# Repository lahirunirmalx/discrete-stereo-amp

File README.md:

# Stereo class-AB amplifier, discrete 12 V supply, volume and headphone boards

A hobby / learning project: a two-channel 1 W class-AB amplifier built from BC547/BC557/BD139/BD140,
its own transformer-fed discrete supply, a volume board and a headphone board, all on one fab panel. It grew
out of a review of a one-transistor "speaker in the collector" amp, which could not be fixed by changing
values. Every number here comes from ngspice; **no board has been built or measured yet** (revision 1.3 is a
prototype design). Release 2 rebuilt the amp front end for ten times less distortion, closed the supply's
regulation loop, added a VU meter tap and the headphone board. Revision 1.3 is the result of a second design
review: an output inductor for stability into capacitive loads, a fail-safe bias trimmer, input protection on
the amp, a correctly sized supply fuse and a headphone switch rated for speaker current.

| Amp | PSU | Volume | Headphone |
|---|---|---|---|
|  |  |  |  |

More views in [docs/images/](docs/images/): top-down 3D renders and the single-sided layouts. Logo and banner: `logo.svg` / `logo.png` / `logo-1024.png` and `banner.svg` / `banner.png` (1280 x 640, the GitHub social-preview size).

## Schematics

| Amp (both channels) | PSU | Volume | Headphone |
|---|---|---|---|
|  |  |  |  |

PDFs of all four are in the release zip (`schematics/`).

## Boards (2-layer layouts, top view, both copper layers)

| Amp, wide 134 x 86 mm | Amp, compact 100 x 98 mm | PSU 90 x 58 mm | Volume 42 x 26 mm | Headphone 42 x 30 mm |
|---|---|---|---|---|
|  |  |  |  |  |

## What it does

| | |
|---|---|
| Output | 1.2 W into 8 ohm and 1.5 W into 4 ohm at the onset of clipping (per channel, 12 V); 0.29 W into 8 ohm at 0.02 to 0.05% THD, 52 mW into 4 ohm at 0.013% |
| Gain / input | 23 (27 dB), 46k input impedance, for a 10k log pot |
| Idle current | output stage 21 mA per channel after setting the trimmer (7 to 10 mV across a 0.47 ohm emitter resistor; trimmer range 2 to 70 mA); about 33 mA per channel from the supply |
| Bandwidth | 20 Hz (8 ohm) / 34 Hz (4 ohm) to 108 kHz, -0.13 dB at 20 kHz |
| Stability | loop phase margin 65 degrees or more for any load from open to 2.2 uF (2.2 uH + 10 ohm output inductor) |
| Protection | amp: resettable fuse + reverse-polarity diode on the 12 V input, bias trimmer limited to 70 mA and fail-safe; PSU: 2 A clamp + 1.6 A slow fuse |
| Supply | 12 to 15 VAC transformer (1.5 A for full power) or 12 V DC in; closed-loop 12.0 V out (trimmer 11.4 to 12.7 V), 0.14 V dip on a 1 A step, 2 A clamp |
| Headphones | DPDT toggle switch speakers / phones, 120 ohm series (8 mW into 32 ohm), DIRECT jumpers, 3.5 mm jack or panel jack header |
| VU meter | 1x3 header on the amp, 1k in series with each speaker node (2.8 Vrms at 1 W) |
| Boards | amp 134 x 86 mm (or the compact 100 x 98 mm variant for the 100 x 100 fab tier), PSU 90 x 58 mm, volume 42 x 26 mm, headphone 42 x 30 mm; 2-layer panel 156 x 156 mm; single-sided variants |
| Parts | 151 through-hole parts with 1206 / SOD / SMA / SOT-23 twins on the same pads; 38 solder jumpers (output pinouts, headphone DIRECT) |

## Design rules this project keeps

1. **Modular.** Every board works alone; none depends on another. Build the amp only, add the volume board or the PSU later.
2. **Your parts, your build.** Every passive has through-hole pads plus a 1206 / SOD / SMA twin; every output transistor sits behind a 3x3 solder-jumper pinout block; the BOM lists at least three substitutes per transistor. Fit what you have.
3. **Debuggable by a beginner.** Every board carries labelled test points with the expected voltage printed next to them, and the bring-up guide walks through them in order.

Any change to this project is checked against these three before it is merged.

## Build it board by board

Every board works on its own; nothing is required by another board.

| You build | You need | What you get |
|---|---|---|
| Amp only | any 12 V DC supply of 1 A (wall adapter, bench supply) into "12V IN"; a phone, PC or DAC into the "IN L G R" header; speakers on the terminals | a working stereo amp; the source's own volume control sets the level (a phone at full volume will clip, so turn it down) |
| Amp + volume board | as above, plus the two 3-pin cables | a volume knob (and the front-panel LED position) |
| Amp + PSU | a 12 to 15 VAC transformer into the PSU, or 12 V DC into its "DC IN"; PSU "DC OUT" to the amp | a regulated, clamped, fused supply with the power LED |
| Amp + headphone board | three wires from the amp's speaker terminals to "FROM AMP", speakers on the headphone board's terminals | a speakers / phones switch and a jack |
| VU meters | any meter on the amp's "VU L G R" header | level display; nothing else changes |
| All four | the panel | the complete desk amp |

Two amp layouts carry the same circuit: the wide one (134 x 86 mm, matches the PSU plus headphone-and-volume
column on the panel) and the compact one (100 x 98 mm, fits JLCPCB's 100 x 100 mm tier when ordered alone).
Choose by price; there is no electrical difference.

## Documents

1. [docs/01-theory-of-operation.md](docs/01-theory-of-operation.md): every block explained for a first build, with the voltages to expect.
2. [docs/02-simulation-results.md](docs/02-simulation-results.md): all the ngspice tables, including the rejected candidates, the release 2 front end and supply (2.7 to 2.9) and the revision 1.3 loop-gain work (2.10).
3. [docs/03-design-review.md](docs/03-design-review.md): what was checked, what was found, what is not verified.
4. [docs/04-build-and-bringup.md](docs/04-build-and-bringup.md): assembly order, first power-up, bias setting, test points, troubleshooting.
5. [ORDER_GUIDE.md](ORDER_GUIDE.md): ordering the panel, substitutes, matching, tolerances.
6. [docs/05-preamp-study.md](docs/05-preamp-study.md): does a preamp stage help a line-level desk amp? (No; where it would.)
7. [docs/KNOWN_ISSUES.md](docs/KNOWN_ISSUES.md) and [docs/CHANGELOG.md](docs/CHANGELOG.md).
8. Interactive: [amp channel in CircuitJS](https://www.falstad.com/circuit/circuitjs.html?cct=$%201%200.000005%2010.20027730826997%2050%205%2050%0Av%2064%20480%2064%2064%200%200%2040%2012%200%200%200.5%0Ag%2064%20480%2064%20512%200%0Aw%2064%2064%20208%2064%200%0Aw%20208%2064%20288%2064%200%0Aw%20288%2064%20352%2064%200%0Aw%20352%2064%20528%2064%200%0Aw%20528%2064%20816%2064%200%0Av%20128%20480%20128%20368%200%201%201000%200.1%200%200%200.5%0Ag%20128%20480%20128%20512%200%0Ar%20128%20368%20192%20368%200%202500%0Ac%20192%20368%20256%20368%200%202.2e-06%200%200%0Ar%20208%2064%20208%20176%200%2047000%0Ar%20208%20176%20208%20480%200%2047000%0Ag%20208%20480%20208%20512%200%0Ac%20240%20176%20240%20480%200%204.7e-05%200%200%0Ag%20240%20480%20240%20512%200%0Aw%20208%20176%20240%20176%200%0Aw%20240%20176%20272%20176%200%0Ar%20272%20176%20272%20368%200%2047000%0Aw%20256%20368%20272%20368%200%0Aw%20272%20368%20304%20368%200%0At%20304%20368%20352%20368%200%201%200%200%20290%0At%20496%20368%20448%20368%200%201%200%200%20290%0Aw%20352%20384%20352%20416%200%0Aw%20352%20416%20400%20416%200%0Aw%20400%20416%20448%20416%200%0Aw%20448%20384%20448%20416%200%0Ar%20400%20416%20400%20480%200%2010000%0Ag%20400%20480%20400%20512%200%0Aw%20448%20352%20448%20320%200%0Aw%20448%20320%20528%20320%200%0Aw%20528%20320%20528%2064%200%0Ar%20288%2064%20288%20160%200%204700%0Aw%20288%20160%20288%20192%200%0Aw%20288%20192%20288%20240%200%0Aw%20288%20240%20352%20240%200%0Aw%20352%20240%20352%20352%200%0Aw%20496%20368%20528%20368%200%0Aw%20528%20368%20544%20368%200%0Ar%20544%20368%20608%20368%200%2022000%0A207%20608%20368%20640%20368%204%20out%0Ar%20528%20368%20528%20416%200%201000%0Ac%20528%20416%20528%20480%200%200.00022%200%200%0Ag%20528%20480%20528%20512%200%0At%20320%20192%20368%20192%200%20-1%200%200%20250%0Aw%20288%20192%20320%20192%200%0Ar%20352%2064%20352%20128%200%2047%0Aw%20352%20128%20368%20128%200%0Aw%20368%20128%20368%20176%200%0Aw%20368%20208%20368%20256%200%0Aw%20368%20256%20400%20256%200%0Aw%20400%20256%20608%20256%200%0Aw%20608%20256%20624%20256%200%0Aw%20624%20256%20736%20256%200%0Ac%20400%20192%20400%20256%200%201e-10%200%200%0A207%20400%20192%20432%20192%204%20c1%0A207%20288%20160%20256%20160%204%20c1%0Ar%20624%20256%20624%20304%200%20820%0At%20560%20304%20608%20304%200%201%200%200%20290%0Aw%20608%20288%20608%20256%200%0Aw%20560%20304%20560%20336%200%0Aw%20560%20336%20624%20336%200%0Aw%20624%20304%20624%20336%200%0Ar%20624%20336%20624%20400%200%201000%0Aw%20608%20320%20608%20400%200%0Aw%20608%20400%20624%20400%200%0Aw%20624%20400%20688%20400%200%0Aw%20688%20400%20736%20400%200%0Ar%20688%20400%20688%20448%200%20270%0Ar%20688%20448%20688%20480%200%20270%0Ag%20688%20480%20688%20512%200%0Ac%20688%20448%20752%20448%200%200.0001%200%200%0A207%20752%20448%20784%20448%204%20out%0At%20736%20256%20784%20256%200%201%200%200%20120%0Aw%20784%20240%20816%20240%200%0Aw%20816%20240%20816%2064%200%0At%20736%20400%20784%20400%200%20-1%200%200%20100%0Ag%20784%20416%20784%20448%200%0Ar%20784%20272%20784%20320%200%200.47%0Ar%20784%20384%20784%20320%200%200.47%0Aw%20784%20320%20848%20320%200%0Aw%20848%20320%20880%20320%200%0Aw%20880%20320%20912%20320%200%0A207%20848%20320%20848%20288%204%20out%0Ar%20880%20320%20880%20400%200%2010%0Ac%20880%20400%20880%20480%200%201e-07%200%200%0Ag%20880%20480%20880%20512%200%0Ac%20912%20320%20976%20320%200%200.001%200%200%0Ar%20976%20320%20976%20480%200%208%0Ag%20976%20480%20976%20512%200%0Ax%2064%20544%2064%20544%204%2016%20Stereo%20amp%20channel%20%28ngspice%20amp_final.cir%29:%20diff%20pair,%20VAS,%20Vbe%20multiplier,%20BD139/BD140.%2012%20V,%20Iq%2021%20mA,%201%20W%20into%208R%20at%200.5%25%20THD%0A), [power supply in CircuitJS](https://www.falstad.com/circuit/circuitjs.html?cct=$%201%200.00002%2010.20027730826997%2050%205%2050%0Av%2064%20352%2064%20160%200%201%2050%2021.2%200%200%200.5%0Ar%2064%20160%20144%20160%200%200.02%0Ar%2064%20352%20144%20352%200%200.8%0Aw%20144%20160%20160%20160%200%0Aw%20144%20352%20240%20352%200%0Ad%20160%20160%20160%2096%200%20default%0Ad%20160%20256%20160%20160%200%20default%0Ag%20160%20256%20160%20288%200%0Ad%20240%20352%20240%2096%200%20default%0Ad%20240%20416%20240%20352%200%20default%0Ag%20240%20416%20240%20448%200%0Aw%20160%2096%20240%2096%200%0Aw%20240%2096%20320%2096%200%0Aw%20320%2096%20368%2096%200%0Aw%20368%2096%20416%2096%200%0Aw%20416%2096%20480%2096%200%0Aw%20480%2096%20624%2096%200%0Aw%20624%2096%20720%2096%200%0Aw%20720%2096%20768%2096%200%0Ac%20320%2096%20320%20416%200%200.0022%200%200%0Ag%20320%20416%20320%20448%200%0Ac%20368%2096%20368%20416%200%200.0022%200%200%0Ag%20368%20416%20368%20448%200%0Ar%20416%2096%20416%20416%200%204700%0Ag%20416%20416%20416%20448%200%0Ar%20480%2096%20480%20192%200%201000%0Az%20480%20320%20480%20192%202%20default-zener%0Ag%20480%20320%20480%20352%200%0Ac%20528%20192%20528%20416%200%200.0001%200%200%0Ag%20528%20416%20528%20448%200%0Aw%20480%20192%20528%20192%200%0Aw%20528%20192%20576%20192%200%0A207%20480%20192%20448%20224%204%20vz%0At%20576%20192%20624%20192%200%201%200%200%20290%0Aw%20624%20176%20624%2096%200%0Aw%20624%20208%20624%20256%200%0Aw%20624%20256%20672%20256%200%0At%20672%20256%20720%20256%200%201%200%200%2060%0Aw%20720%20240%20720%2096%200%0Ar%20720%20272%20720%20352%200%200.33%0Aw%20720%20272%20768%20272%200%0At%20768%20272%20816%20272%200%201%200%200%20290%0A207%20816%20256%20848%20240%204%20vz%0Aw%20816%20288%20816%20352%200%0Aw%20816%20352%20768%20352%200%0Aw%20768%20352%20720%20352%200%0Ad%20768%20352%20768%2096%200%20default%0Aw%20816%20352%20864%20352%200%0Aw%20864%20352%20912%20352%200%0Aw%20912%20352%20960%20352%200%0Aw%20960%20352%201056%20352%200%0Ac%20864%20352%20864%20416%200%200.00022%200%200%0Ag%20864%20416%20864%20448%200%0Ar%20912%20352%20912%20384%200%201000%0A162%20912%20384%20912%20416%202%20default-led%201%200%200%200.01%0Ag%20912%20416%20912%20448%200%0Ad%201040%20352%20960%20352%200%20default%0As%201072%20352%201040%20352%200%201%20false%0Av%201072%20416%201072%20352%200%200%2040%2012%200%200%200.5%0Ag%201072%20416%201072%20448%200%0Ar%201056%20352%201056%20416%200%2015%0Ag%201056%20416%201056%20448%200%0Ax%2064%20480%2064%20480%204%2016%20Discrete%2012%20V%20PSU%20%28ngspice%20psu.cir%29.%20Zener%20drawn%20with%20the%20default%205.6%20V%20model:%20double-click%20it%20and%20set%2013%20V.%20Close%20the%20switch%20to%20test%20the%20DC-in%20path.%0A) (text netlists in [docs/circuitjs/](docs/circuitjs/)).
9. [docs/stereo-amp-notes.html](docs/stereo-amp-notes.html): single-file bench-notes page with the verified figures, every sweep table and links to interactive CircuitJS versions of the channel and the supply (download and open locally, or view it through htmlpreview.github.io).

## Files

| Dir | What |
|---|---|
| `sim/` | ngspice decks and results (`sim/README.md`) |
| `kicad/gen_amp.py gen_psu.py gen_vol.py gen_hp.py` | schematic generators (kisch.py writer, common.py helpers and the STAMP); `netcheck.py` proves each netlist matches its deck |
| `kicad/gen_pcb_*.py`, `pcbgen.py` | placement + board builder (hybrid footprints, 2-layer or `--single`) |
| `kicad/build.sh <board> [--single] [--compact]` | place, freerouting (second pass if needed), ground pour, DRC, PNG |
| `kicad/panel/` | KiKit multi-design panel, BOMs (bom_all, bom_shopping, bom_mouser) |
| `kicad/release.sh` | fab package -> `release/stereo-amp-release-<date>.zip` |
| `docs/` | the documents above and `docs/images/` |
| `analysis/` | check-schematic / check-pcb analyzer outputs used by the design review |
| `build_all.sh` | regenerate everything |

Schematic symbol UUIDs are deterministic, so re-running a generator keeps PCB parity. Edit the generators,
not the KiCad files.

## Status

Revision 1.3, 2026-11-10: design complete, simulated, reviewed twice, DRC clean (2-layer boards and panel), unbuilt. The
single-sided amp board needs hand finishing (see known issues).

## License

[CC BY-NC-SA 4.0](LICENSE): build it, modify it, share it with credit; no commercial use of this or any
derived design without the author's written permission.

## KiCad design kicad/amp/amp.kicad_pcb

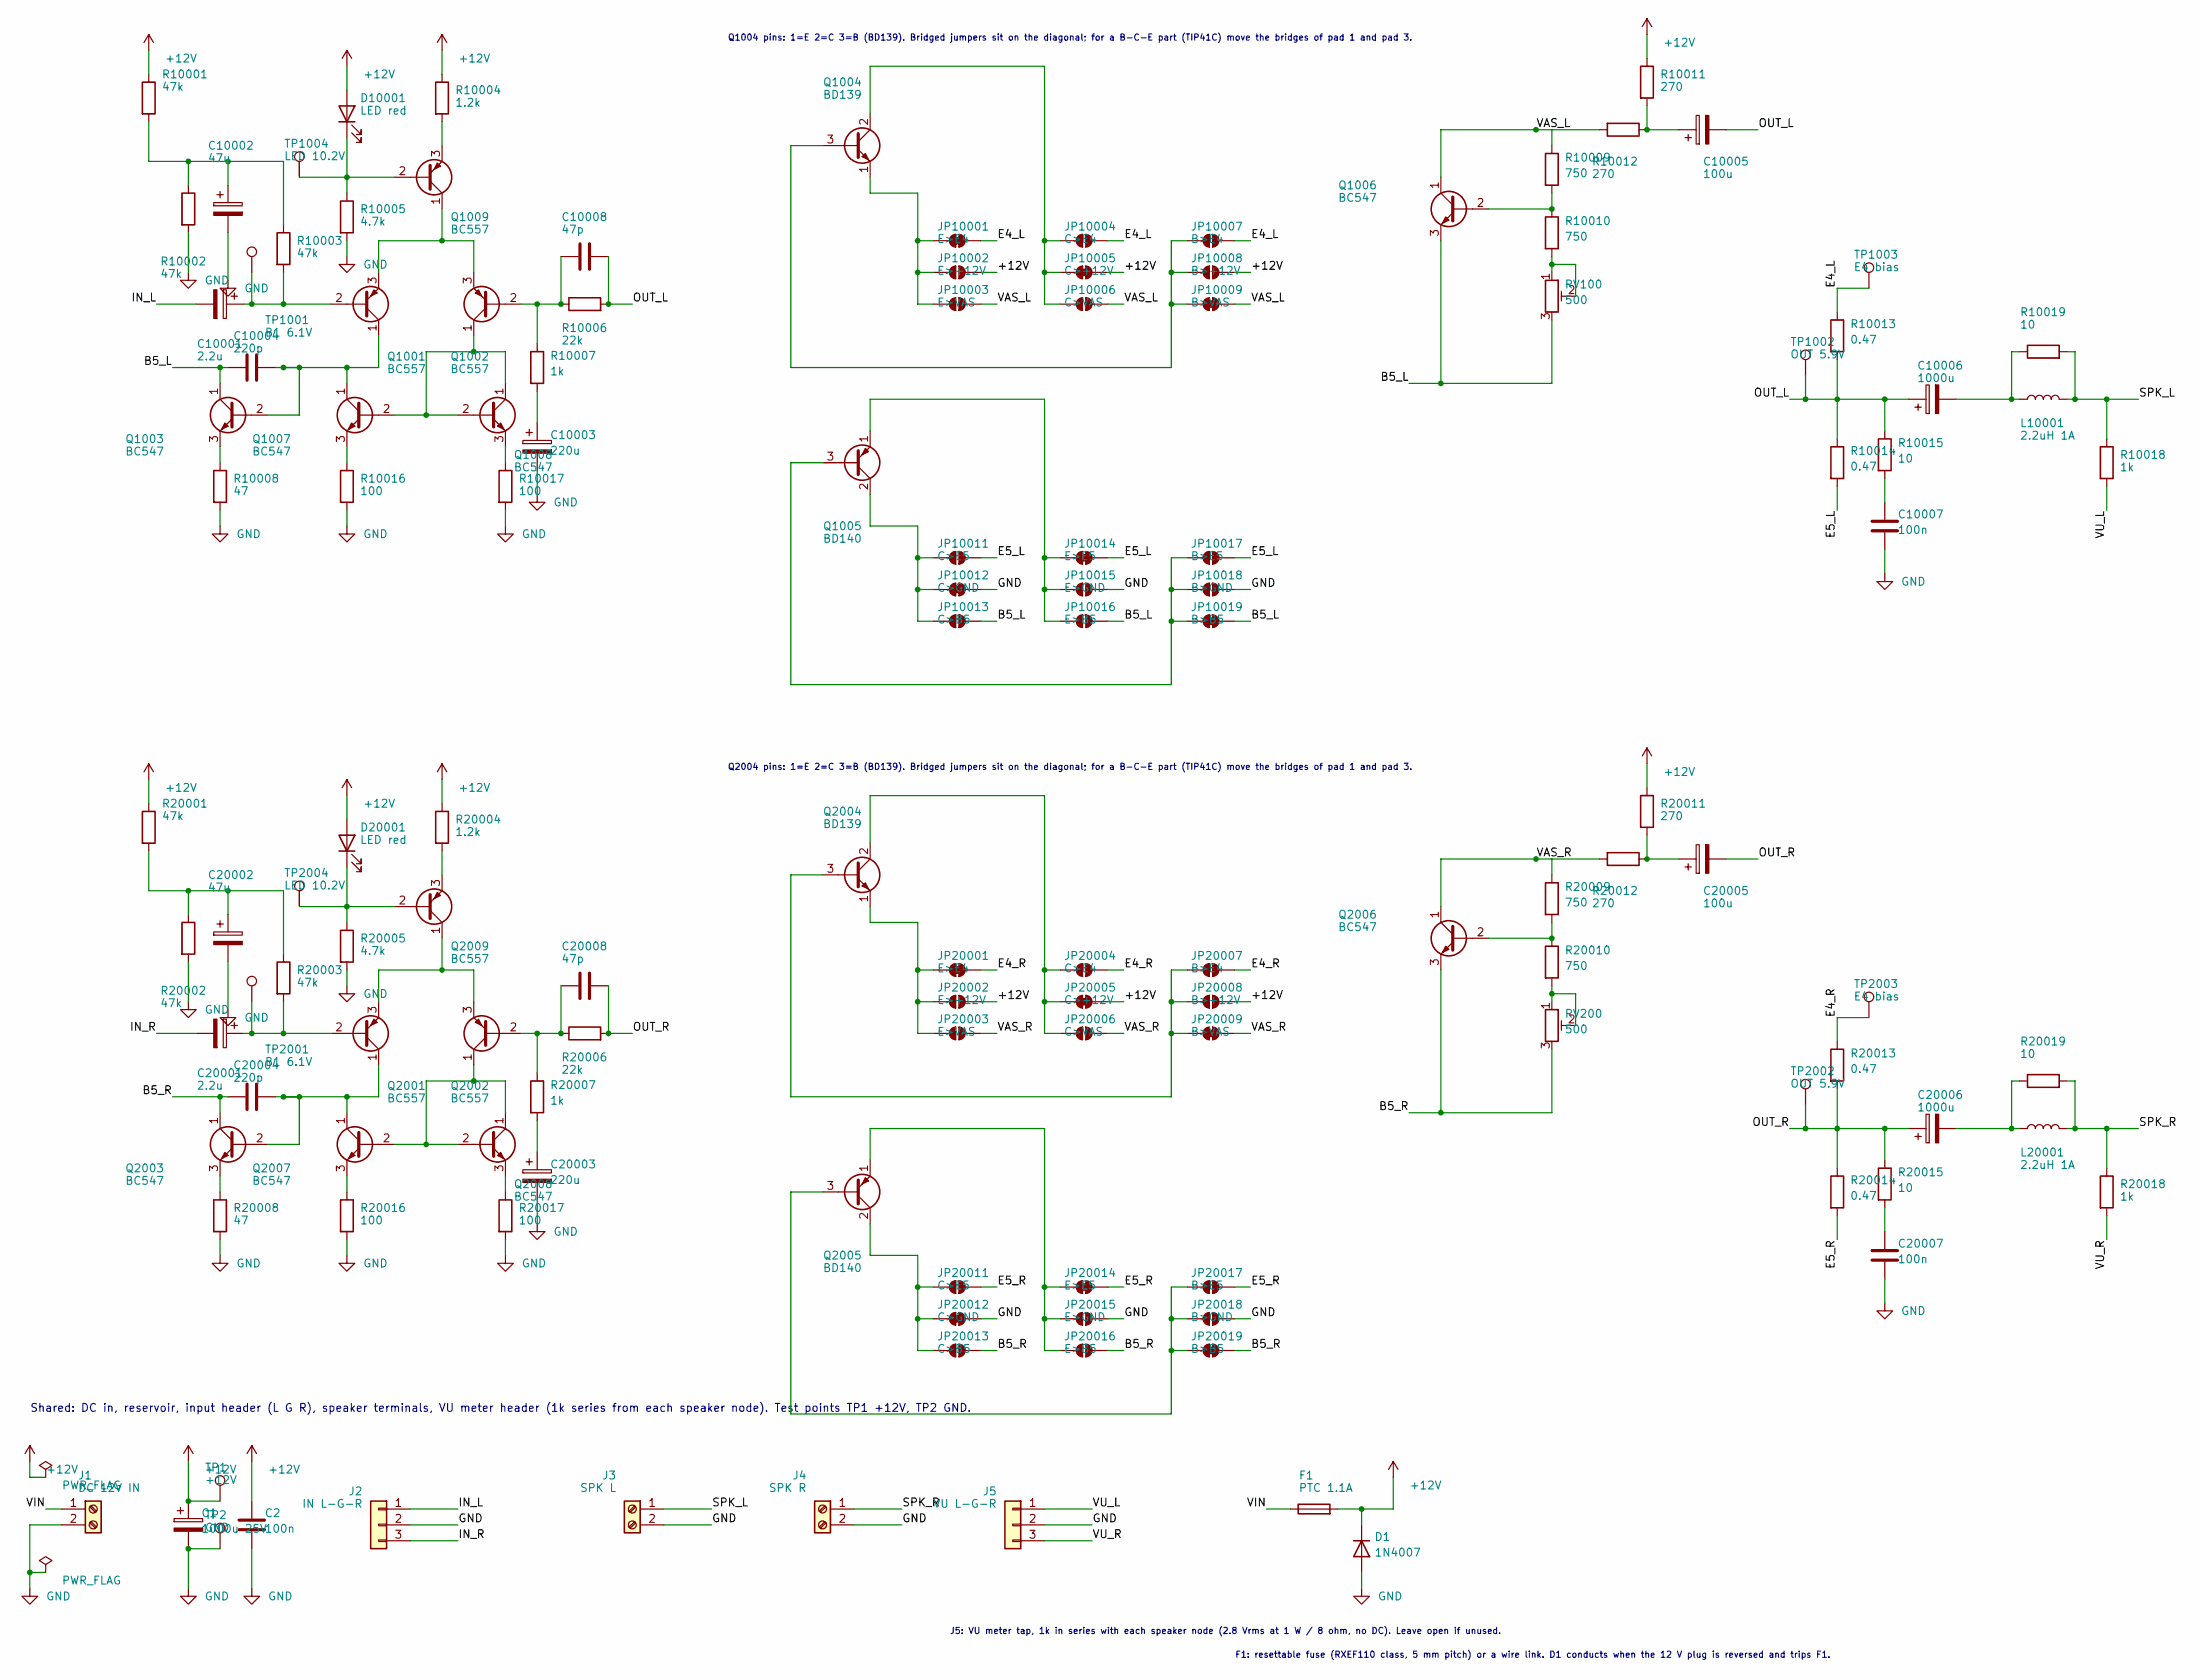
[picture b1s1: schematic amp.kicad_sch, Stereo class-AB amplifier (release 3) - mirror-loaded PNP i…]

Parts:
C1: 1000u 25V; CP_Radial_D10.0mm_P5.00mm
C2, C10007, C20007: 100n; C_P5_1206
C10001, C20001: 2.2u; CE_P2_1206
C10002, C20002: 47u; CE_P2_1206
C10003, C20003: 220u; CP_Radial_D6.3mm_P2.50mm
C10004, C20004: 220p; C_P5_1206
C10005, C20005: 100u; CP_Radial_D6.3mm_P2.50mm
C10006, C20006: 1000u; CP_Radial_D8.0mm_P3.50mm
C10008, C20008: 47p; C_P5_1206
D1: 1N4007; D_DO41_SMA
D10001, D20001: LED red; LED_D3_1206
F1: PTC 1.1A; C_P5_1206
J1: DC 12V IN; TerminalBlock_Phoenix_MKDS-1,5-2-5.08_1x02_P5.08mm_Horizont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
J2: IN L-G-R; PinHeader_1x03_P2.54mm_Vertical
J3: SPK L; TerminalBlock_Phoenix_MKDS-1,5-2-5.08_1x02_P5.08mm_Horizont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
J4: SPK R; TerminalBlock_Phoenix_MKDS-1,5-2-5.08_1x02_P5.08mm_Horizont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
J5: VU L-G-R; PinHeader_1x03_P2.54mm_Vertical
JP10001, JP20001: E>E4; SolderJumper-2_P1.3mm_Bridged_Pad1.0x1.5mm
JP10002, JP20002: E>+12V; SolderJumper-2_P1.3mm_Open_Pad1.0x1.5mm
JP10003, JP20003: E>VAS; SolderJumper-2_P1.3mm_Open_Pad1.0x1.5mm
JP10004, JP20004: C>E4; SolderJumper-2_P1.3mm_Open_Pad1.0x1.5mm
JP10005, JP20005: C>+12V; SolderJumper-2_P1.3mm_Bridged_Pad1.0x1.5mm
JP10006, JP20006: C>VAS; SolderJumper-2_P1.3mm_Open_Pad1.0x1.5mm
JP10007, JP20007: B>E4; SolderJumper-2_P1.3mm_Open_Pad1.0x1.5mm
JP10008, JP20008: B>+12V; SolderJumper-2_P1.3mm_Open_Pad1.0x1.5mm
JP10009, JP20009: B>VAS; SolderJumper-2_P1.3mm_Bridged_Pad1.0x1.5mm
JP10011, JP20011: C>E5; SolderJumper-2_P1.3mm_Open_Pad1.0x1.5mm
JP10012, JP20012: C>GND; SolderJumper-2_P1.3mm_Bridged_Pad1.0x1.5mm
JP10013, JP20013: C>B5; SolderJumper-2_P1.3mm_Open_Pad1.0x1.5mm
JP10014, JP20014: E>E5; SolderJumper-2_P1.3mm_Bridged_Pad1.0x1.5mm
JP10015, JP20015: E>GND; SolderJumper-2_P1.3mm_Open_Pad1.0x1.5mm
JP10016, JP20016: E>B5; SolderJumper-2_P1.3mm_Open_Pad1.0x1.5mm
JP10017, JP20017: B>E5; SolderJumper-2_P1.3mm_Open_Pad1.0x1.5mm
JP10018, JP20018: B>GND; SolderJumper-2_P1.3mm_Open_Pad1.0x1.5mm
JP10019, JP20019: B>B5; SolderJumper-2_P1.3mm_Bridged_Pad1.0x1.5mm
L10001, L20001: 2.2uH 1A; R_Axial_1206
Q1001, Q1002, Q1009, Q2001, Q2002, Q2009: BC557; TO92_SOT23
Q1003, Q1006, Q1007, Q1008, Q2003, Q2006, Q2007, Q2008: BC547; TO92_SOT23
Q1004, Q2004: BD139; TO-220-3_Vertical
Q1005, Q2005: BD140; TO-220-3_Vertical
R10001, R10002, R10003, R20001, R20002, R20003: 47k; R_Axial_1206
R10004, R20004: 1.2k; R_Axial_1206
R10005, R20005: 4.7k; R_Axial_1206
R10006, R20006: 22k; R_Axial_1206
R10007, R10018, R20007, R20018: 1k; R_Axial_1206
R10008, R20008: 47; R_Axial_1206
R10009, R10010, R20009, R20010: 750; R_Axial_1206
R10011, R10012, R20011, R20012: 270; R_Axial_1206
R10013, R10014, R20013, R20014: 0.47; R_Axial_DIN0414_L11.9mm_D4.5mm_P15.24mm_Horizontal
R10015, R10019, R20015, R20019: 10; R_Axial_1206
R10016, R10017, R20016, R20017: 100; R_Axial_1206
RV100, RV200: 500; Potentiometer_Bourns_3296W_Vertical
TP1: +12V; TestPoint_Loop_D2.50mm_Drill1.0mm
TP2: GND; TestPoint_Loop_D2.50mm_Drill1.0mm
TP1001, TP2001: B1 6.1V; TestPoint_Loop_D2.50mm_Drill1.0mm
TP1002, TP2002: OUT 5.9V; TestPoint_Loop_D2.50mm_Drill1.0mm
TP1003, TP2003: E4 bias; TestPoint_Loop_D2.50mm_Drill1.0mm
TP1004, TP2004: LED 10.2V; TestPoint_Loop_D2.50mm_Drill1.0mm

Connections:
+12V: C1.1, C2.1, C2.1S, D1.1 (K), D1.1S, D10001.2 (A), D10001.2S, D20001.2 (A), D20001.2S, F1.2, F1.2S, JP10002.2 (B), JP10005.2 (B), JP10008.2 (B), JP20002.2 (B), JP20005.2 (B), JP20008.2 (B), R10001.1, R10001.1S, R10004.1, R10004.1S, R10011.1, R10011.1S, R20001.1, R20001.1S, R20004.1, R20004.1S, R20011.1, R20011.1S, TP1.1
/B5_L: C10004.1, C10004.1S, JP10013.2 (B), JP10016.2 (B), JP10019.2 (B), Q1003.1 (C), Q1003.1S, Q1006.3 (E), Q1006.3S, RV100.3
/B5_R: C20004.1, C20004.1S, JP20013.2 (B), JP20016.2 (B), JP20019.2 (B), Q2003.1 (C), Q2003.1S, Q2006.3 (E), Q2006.3S, RV200.3
/E4_L: JP10001.2 (B), JP10004.2 (B), JP10007.2 (B), R10013.1, TP1003.1
/E4_R: JP20001.2 (B), JP20004.2 (B), JP20007.2 (B), R20013.1, TP2003.1
/E5_L: JP10011.2 (B), JP10014.2 (B), JP10017.2 (B), R10014.2
/E5_R: JP20011.2 (B), JP20014.2 (B), JP20017.2 (B), R20014.2
/IN_L: C10001.2, C10001.2S, J2.1
/IN_R: C20001.2, C20001.2S, J2.3
/OUT_L: C10005.2, C10006.1, C10008.2, C10008.2S, R10006.2, R10006.2S, R10013.2, R10014.1, R10015.1, R10015.1S, TP1002.1
/OUT_R: C20005.2, C20006.1, C20008.2, C20008.2S, R20006.2, R20006.2S, R20013.2, R20014.1, R20015.1, R20015.1S, TP2002.1
/SPK_L: J3.1, L10001.2, L10001.2S, R10018.1, R10018.1S, R10019.2, R10019.2S
/SPK_R: J4.1, L20001.2, L20001.2S, R20018.1, R20018.1S, R20019.2, R20019.2S
/VAS_L: JP10003.2 (B), JP10006.2 (B), JP10009.2 (B), Q1006.1 (C), Q1006.1S, R10009.1, R10009.1S, R10012.2, R10012.2S
/VAS_R: JP20003.2 (B), JP20006.2 (B), JP20009.2 (B), Q2006.1 (C), Q2006.1S, R20009.1, R20009.1S, R20012.2, R20012.2S
/VIN: F1.1, F1.1S, J1.1
/VU_L: J5.1, R10018.2, R10018.2S
/VU_R: J5.3, R20018.2, R20018.2S
GND: C1.2, C2.2, C2.2S, C10002.2, C10002.2S, C10003.2, C10007.2, C10007.2S, C20002.2, C20002.2S, C20003.2, C20007.2, C20007.2S, D1.2 (A), D1.2S, J1.2, J2.2, J3.2, J4.2, J5.2, JP10012.2 (B), JP10015.2 (B), JP10018.2 (B), JP20012.2 (B), JP20015.2 (B), JP20018.2 (B), R10002.2, R10002.2S, R10005.2, R10005.2S, R10008.2, R10008.2S, R10016.2, R10016.2S, R10017.2, R10017.2S, R20002.2, R20002.2S, R20005.2, R20005.2S, R20008.2, R20008.2S, R20016.2, R20016.2S, R20017.2, R20017.2S, TP2.1
unnamed: C10002.1, C10002.1S, R10001.2, R10001.2S, R10002.1, R10002.1S, R10003.1, R10003.1S
unnamed: C10003.1, R10007.2, R10007.2S
unnamed: C10005.1, R10011.2, R10011.2S, R10012.1, R10012.1S
unnamed: C10006.2, L10001.1, L10001.1S, R10019.1, R10019.1S
unnamed: C10007.1, C10007.1S, R10015.2, R10015.2S
unnamed: C20002.1, C20002.1S, R20001.2, R20001.2S, R20002.1, R20002.1S, R20003.1, R20003.1S
unnamed: C20003.1, R20007.2, R20007.2S
unnamed: C20005.1, R20011.2, R20011.2S, R20012.1, R20012.1S
unnamed: C20006.2, L20001.1, L20001.1S, R20019.1, R20019.1S
unnamed: C20007.1, C20007.1S, R20015.2, R20015.2S
unnamed: D10001.1 (K), D10001.1S, Q1009.2 (B), Q1009.2S, R10005.1, R10005.1S, TP1004.1
unnamed: D20001.1 (K), D20001.1S, Q2009.2 (B), Q2009.2S, R20005.1, R20005.1S, TP2004.1
unnamed: JP10001.1 (A), JP10002.1 (A), JP10003.1 (A), Q1004.1 (E)
unnamed: JP10004.1 (A), JP10005.1 (A), JP10006.1 (A), Q1004.2 (C)
unnamed: JP10007.1 (A), JP10008.1 (A), JP10009.1 (A), Q1004.3 (B)
unnamed: JP10011.1 (A), JP10012.1 (A), JP10013.1 (A), Q1005.2 (C)
unnamed: JP10014.1 (A), JP10015.1 (A), JP10016.1 (A), Q1005.1 (E)
unnamed: JP10017.1 (A), JP10018.1 (A), JP10019.1 (A), Q1005.3 (B)
unnamed: JP20001.1 (A), JP20002.1 (A), JP20003.1 (A), Q2004.1 (E)
unnamed: JP20004.1 (A), JP20005.1 (A), JP20006.1 (A), Q2004.2 (C)
unnamed: JP20007.1 (A), JP20008.1 (A), JP20009.1 (A), Q2004.3 (B)
unnamed: JP20011.1 (A), JP20012.1 (A), JP20013.1 (A), Q2005.2 (C)
unnamed: JP20014.1 (A), JP20015.1 (A), JP20016.1 (A), Q2005.1 (E)
unnamed: JP20017.1 (A), JP20018.1 (A), JP20019.1 (A), Q2005.3 (B)
unnamed: C10001.1, C10001.1S, Q1001.2 (B), Q1001.2S, R10003.2, R10003.2S, TP1001.1
unnamed: C10004.2, C10004.2S, Q1001.1 (C), Q1001.1S, Q1003.2 (B), Q1003.2S, Q1007.1 (C), Q1007.1S
unnamed: Q1001.3 (E), Q1001.3S, Q1002.3 (E), Q1002.3S, Q1009.1 (C), Q1009.1S
unnamed: C10008.1, C10008.1S, Q1002.2 (B), Q1002.2S, R10006.1, R10006.1S, R10007.1, R10007.1S
unnamed: Q1002.1 (C), Q1002.1S, Q1007.2 (B), Q1007.2S, Q1008.1 (C), Q1008.1S, Q1008.2 (B), Q1008.2S
unnamed: Q1003.3 (E), Q1003.3S, R10008.1, R10008.1S
unnamed: Q1006.2 (B), Q1006.2S, R10009.2, R10009.2S, R10010.1, R10010.1S
unnamed: Q1007.3 (E), Q1007.3S, R10016.1, R10016.1S
unnamed: Q1008.3 (E), Q1008.3S, R10017.1, R10017.1S
unnamed: Q1009.3 (E), Q1009.3S, R10004.2, R10004.2S
unnamed: C20001.1, C20001.1S, Q2001.2 (B), Q2001.2S, R20003.2, R20003.2S, TP2001.1
unnamed: C20004.2, C20004.2S, Q2001.1 (C), Q2001.1S, Q2003.2 (B), Q2003.2S, Q2007.1 (C), Q2007.1S
unnamed: Q2001.3 (E), Q2001.3S, Q2002.3 (E), Q2002.3S, Q2009.1 (C), Q2009.1S
unnamed: C20008.1, C20008.1S, Q2002.2 (B), Q2002.2S, R20006.1, R20006.1S, R20007.1, R20007.1S
unnamed: Q2002.1 (C), Q2002.1S, Q2007.2 (B), Q2007.2S, Q2008.1 (C), Q2008.1S, Q2008.2 (B), Q2008.2S
unnamed: Q2003.3 (E), Q2003.3S, R20008.1, R20008.1S
unnamed: Q2006.2 (B), Q2006.2S, R20009.2, R20009.2S, R20010.1, R20010.1S
unnamed: Q2007.3 (E), Q2007.3S, R20016.1, R20016.1S
unnamed: Q2008.3 (E), Q2008.3S, R20017.1, R20017.1S
unnamed: Q2009.3 (E), Q2009.3S, R20004.2, R20004.2S
unnamed: R10010.2, R10010.2S, RV100.1, RV100.2
unnamed: R20010.2, R20010.2S, RV200.1, RV200.2

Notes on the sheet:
Q1004 pins: 1=E 2=C 3=B (BD139). Bridged jumpers sit on the diagonal; for a B-C-E part (TIP41C) move the bridges of pad 1 and pad 3.
Q2004 pins: 1=E 2=C 3=B (BD139). Bridged jumpers sit on the diagonal; for a B-C-E part (TIP41C) move the bridges of pad 1 and pad 3.
Shared: DC in, reservoir, input header (L G R), speaker terminals, VU meter header (1k series from each speaker node). Test points TP1 +12V, TP2 GND.
F1: resettable fuse (RXEF110 class, 5 mm pitch) or a wire link. D1 conducts when the 12 V plug is reversed and trips F1.
J5: VU meter tap, 1k in series with each speaker node (2.8 Vrms at 1 W / 8 ohm, no DC). Leave open if unused.

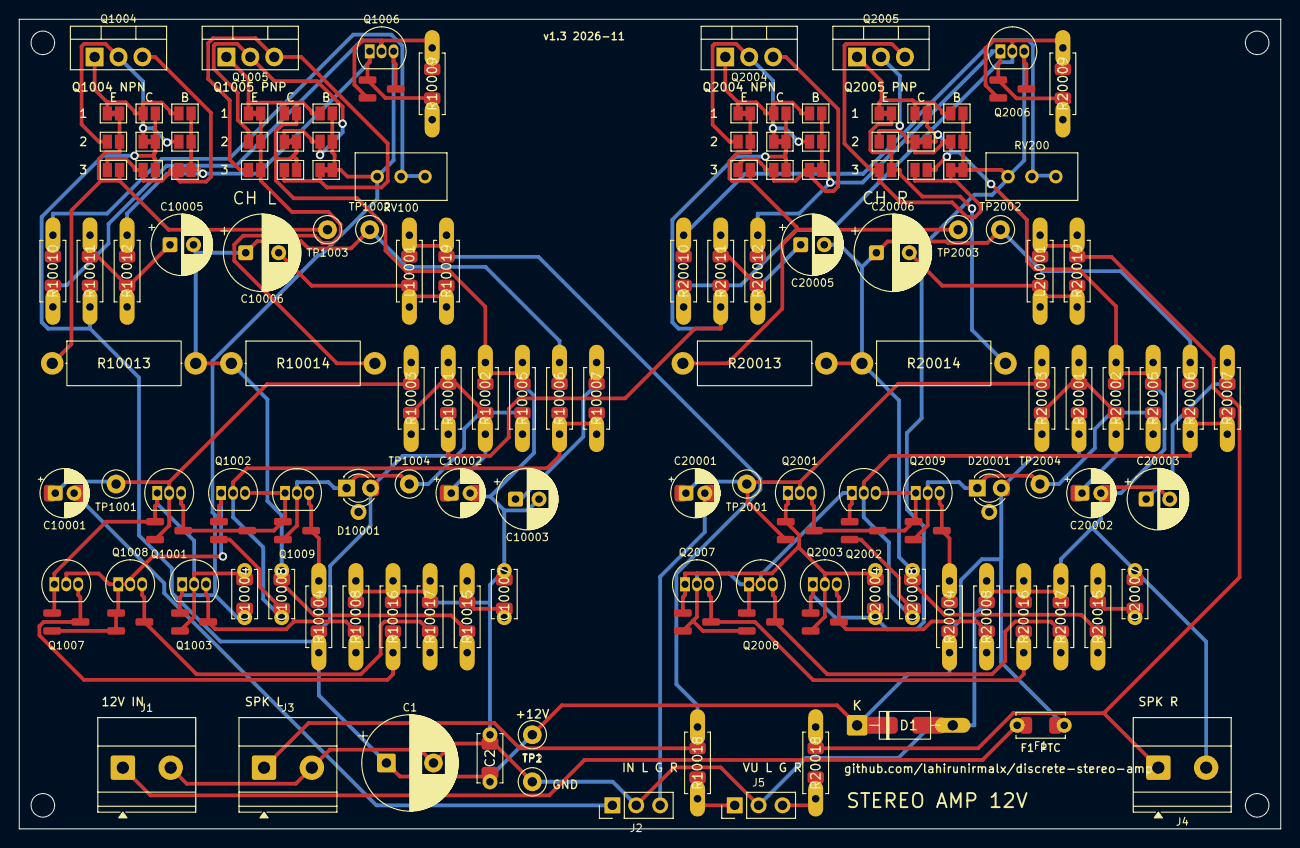
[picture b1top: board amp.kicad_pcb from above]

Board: 2 copper layers, 134.0 x 86.0 mm, 137 parts (0 on the bottom side), 65 nets.

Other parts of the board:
H1, H2, H3, H4: M2.5; Hole_2.5mm

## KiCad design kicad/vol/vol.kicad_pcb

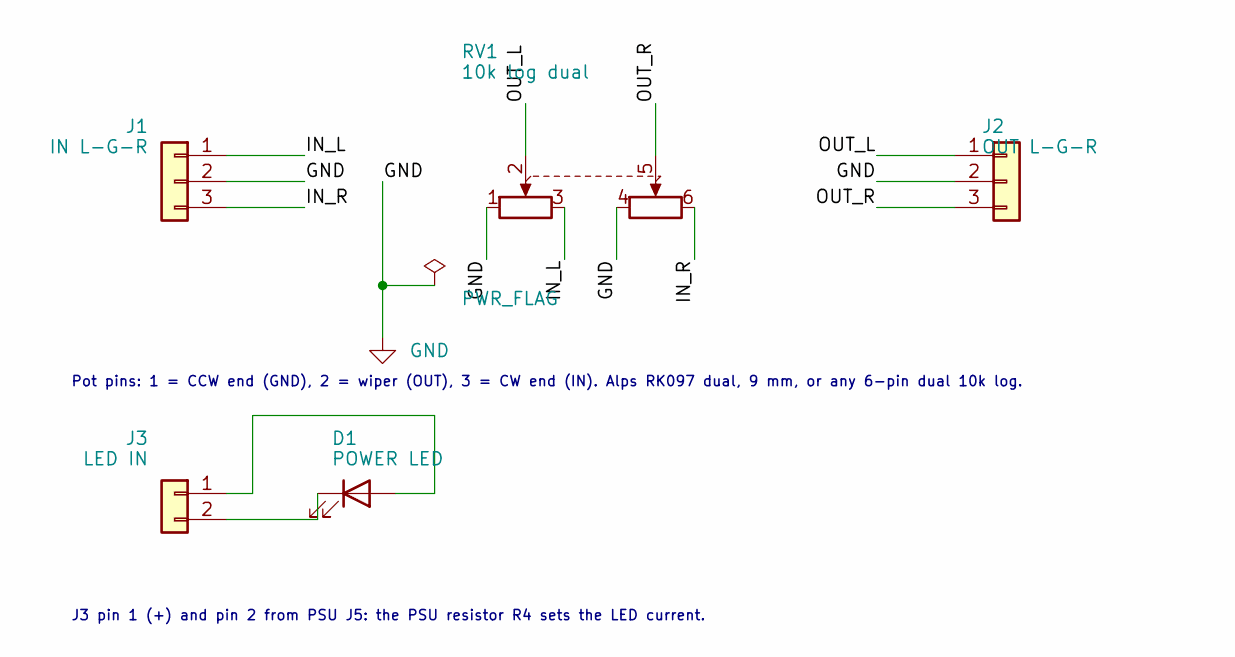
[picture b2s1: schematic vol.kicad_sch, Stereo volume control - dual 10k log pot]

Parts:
D1: POWER LED; LED_D3_1206
J1: IN L-G-R; PinHeader_1x03_P2.54mm_Vertical
J2: OUT L-G-R; PinHeader_1x03_P2.54mm_Vertical
J3: LED IN; PinHeader_1x02_P2.54mm_Vertical
RV1: 10k log dual; Potentiometer_Alps_RK097_Dual_Horizontal

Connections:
/IN_L: J1.1, RV1.3
/IN_R: J1.3, RV1.6
/OUT_L: J2.1, RV1.2
/OUT_R: J2.3, RV1.5
GND: J1.2, J2.2, RV1.1, RV1.4
unnamed: D1.2 (A), D1.2S, J3.1
unnamed: D1.1 (K), D1.1S, J3.2

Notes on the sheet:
J3 pin 1 (+) and pin 2 from PSU J5: the PSU resistor R4 sets the LED current.
Pot pins: 1 = CCW end (GND), 2 = wiper (OUT), 3 = CW end (IN). Alps RK097 dual, 9 mm, or any 6-pin dual 10k log.

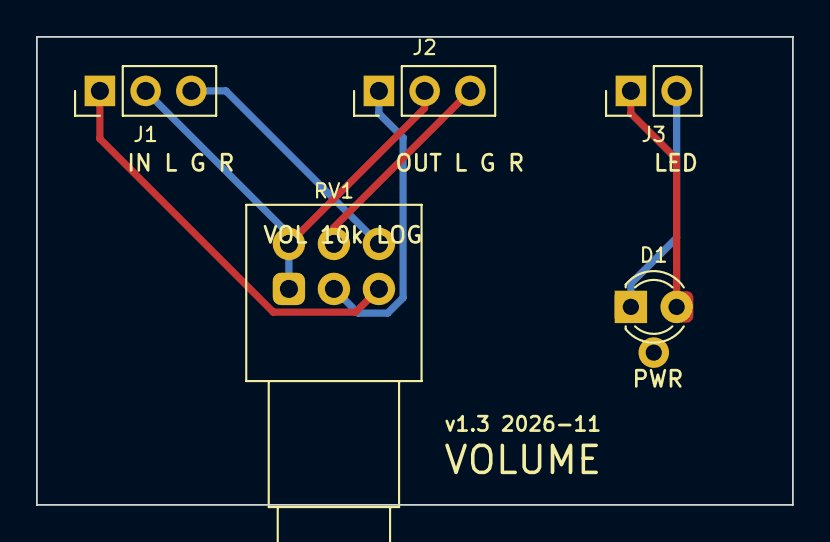
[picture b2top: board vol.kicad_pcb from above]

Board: 2 copper layers, 42.0 x 26.0 mm, 5 parts (0 on the bottom side), 7 nets.

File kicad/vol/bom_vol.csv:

board,qty,refs,value,through_hole,smd_alternative,tolerance_rating,substitutes,matching_note
vol,1,D1,POWER LED,3 mm LED (or two small diodes via the middle hole M),1206 LED,"3 mm LED, any colour",any 3 mm or 5 mm LED,"Front-panel power LED, fed from PSU J5 by two wires (pin 1 = +)."
vol,1,J1,IN L-G-R,PinHeader_1x03_P2.54mm_Vertical,,"5 percent / 20 percent, standard",,
vol,1,J3,LED IN,PinHeader_1x02_P2.54mm_Vertical,,"5 percent / 20 percent, standard",,
vol,1,J2,OUT L-G-R,PinHeader_1x03_P2.54mm_Vertical,,"5 percent / 20 percent, standard",,
vol,1,RV1,10k log dual,Potentiometer_Alps_RK097_Dual_Horizontal,,"10k log (A103) dual, 6 pins, 9 mm",Alps RK097 dual 10k A (fitted); any RK09-style 6-pin dual 10k log; 20k log (slight gain loss at mid travel); 10k linear works but the law feels wrong,"Pin 3 = clockwise end = input, pin 1 = ground, pin 2 = wiper. Clockwise should be louder; if not, swap the outer two wires."

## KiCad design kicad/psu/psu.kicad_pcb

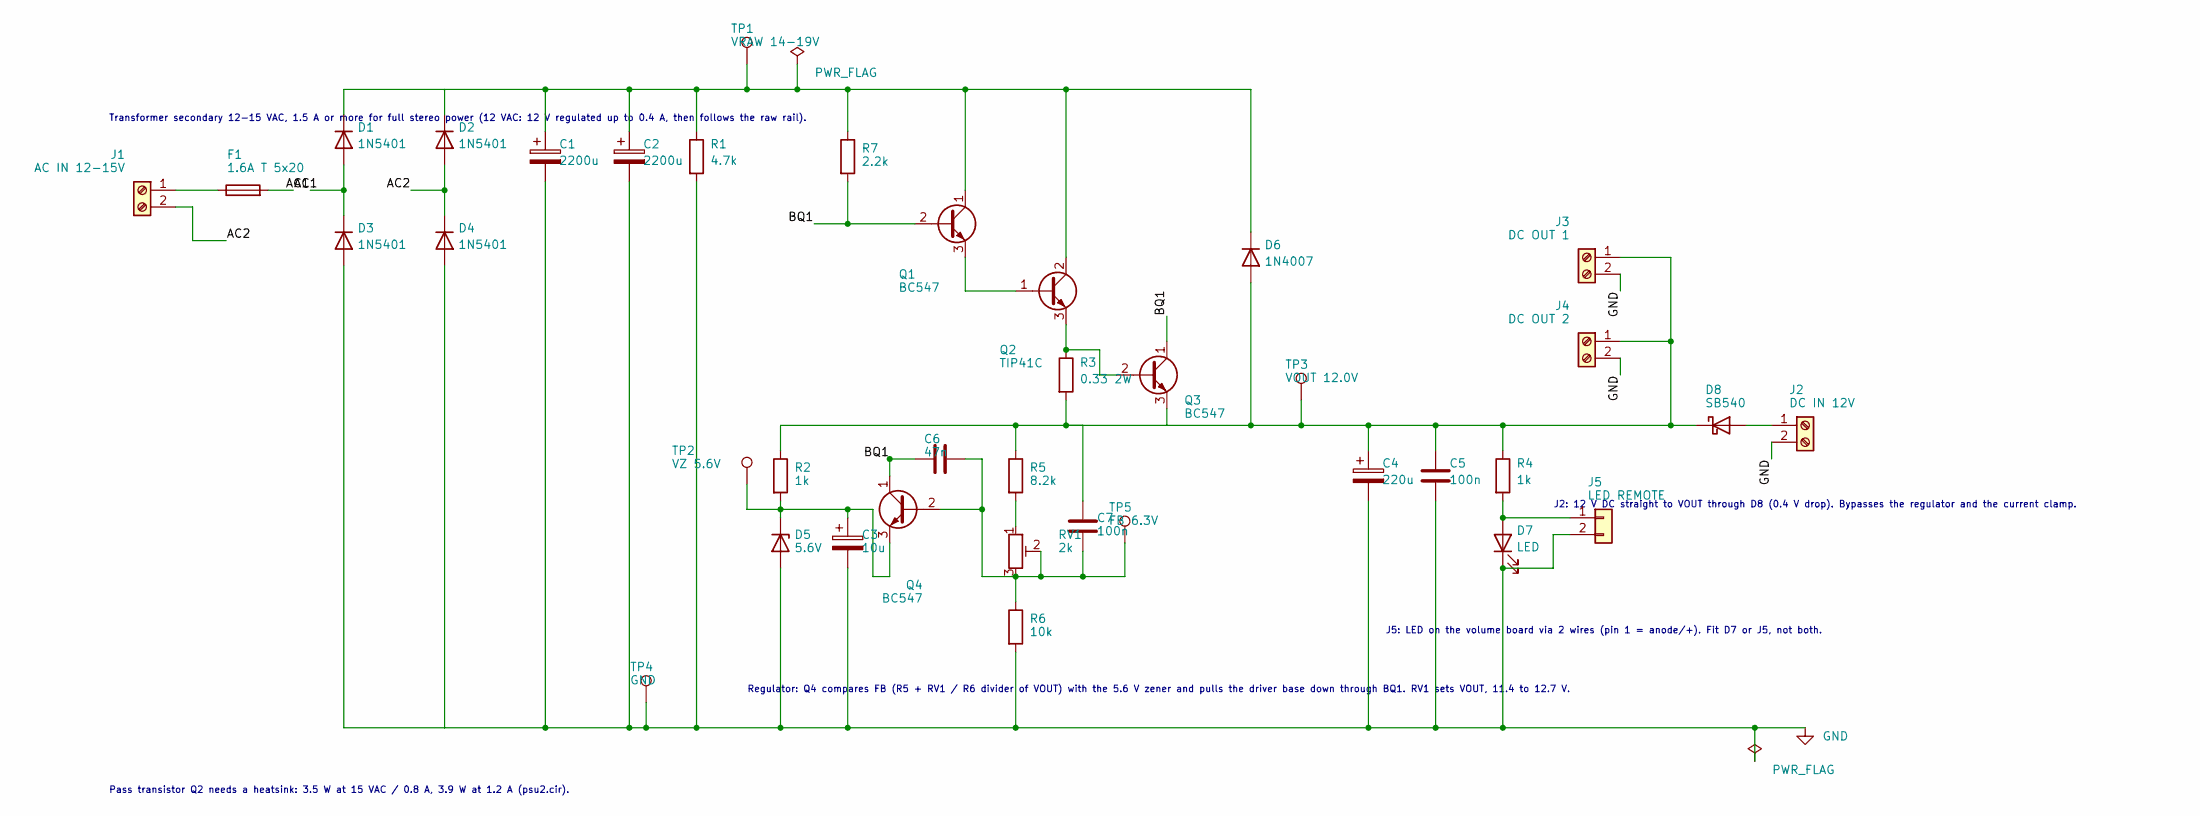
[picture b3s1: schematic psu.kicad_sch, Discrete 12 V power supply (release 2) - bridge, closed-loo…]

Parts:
C1, C2: 2200u; CP_Radial_D13.0mm_P5.00mm
C3: 10u; CE_P2_1206
C4: 220u; CP_Radial_D6.3mm_P2.50mm
C5, C7: 100n; C_P5_1206
C6: 47n; C_P5_1206
D1, D2, D3, D4: 1N5401; D_DO201_SMA
D5: 5.6V; D_DO41_SMA
D6: 1N4007; D_DO41_SMA
D7: LED; LED_D3_1206
D8: SB540; D_DO201_SMA
F1: 1.6A T 5x20; Fuseholder_Clip-5x20mm_Littelfuse_100_Inline_P20.50x4.60mm_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
J1: AC IN 12-15V; TerminalBlock_Phoenix_MKDS-1,5-2-5.08_1x02_P5.08mm_Horizont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
J2: DC IN 12V; TerminalBlock_Phoenix_MKDS-1,5-2-5.08_1x02_P5.08mm_Horizont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
J3: DC OUT 1; TerminalBlock_Phoenix_MKDS-1,5-2-5.08_1x02_P5.08mm_Horizont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
J4: DC OUT 2; TerminalBlock_Phoenix_MKDS-1,5-2-5.08_1x02_P5.08mm_Horizont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
J5: LED REMOTE; PinHeader_1x02_P2.54mm_Vertical
Q1, Q3, Q4: BC547; TO92_SOT23
Q2: TIP41C; TO-220-3_Vertical
R1: 4.7k; R_Axial_1206
R2, R4: 1k; R_Axial_1206
R3: 0.33 2W; R_Axial_DIN0414_L11.9mm_D4.5mm_P15.24mm_Horizontal
R5: 8.2k; R_Axial_1206
R6: 10k; R_Axial_1206
R7: 2.2k; R_Axial_1206
RV1: 2k; Potentiometer_Bourns_3296W_Vertical
TP1: VRAW 14-19V; TestPoint_Loop_D2.50mm_Drill1.0mm
TP2: VZ 5.6V; TestPoint_Loop_D2.50mm_Drill1.0mm
TP3: VOUT 12.0V; TestPoint_Loop_D2.50mm_Drill1.0mm
TP4: GND; TestPoint_Loop_D2.50mm_Drill1.0mm
TP5: FB 6.3V; TestPoint_Loop_D2.50mm_Drill1.0mm

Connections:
/AC1: D1.2 (A), D1.2S, D3.1 (K), D3.1S, F1.2
/AC2: D2.2 (A), D2.2S, D4.1 (K), D4.1S, J1.2
/BQ1: C6.1, C6.1S, Q1.2 (B), Q1.2S, Q3.1 (C), Q3.1S, Q4.1 (C), Q4.1S, R7.2, R7.2S
GND: C1.2, C2.2, C3.2, C3.2S, C4.2, C5.2, C5.2S, D3.2 (A), D3.2S, D4.2 (A), D4.2S, D5.2 (A), D5.2S, D7.1 (K), D7.1S, J2.2, J3.2, J4.2, J5.2, R1.2, R1.2S, R6.2, R6.2S, TP4.1
unnamed: C1.1, C2.1, D1.1 (K), D1.1S, D2.1 (K), D2.1S, D6.1 (K), D6.1S, Q1.1 (C), Q1.1S, Q2.2 (C), R1.1, R1.1S, R7.1, R7.1S, TP1.1
unnamed: C3.1, C3.1S, D5.1 (K), D5.1S, Q4.3 (E), Q4.3S, R2.2, R2.2S, TP2.1
unnamed: C4.1, C5.1, C5.1S, C7.1, C7.1S, D6.2 (A), D6.2S, D8.1 (K), D8.1S, J3.1, J4.1, Q3.3 (E), Q3.3S, R2.1, R2.1S, R3.2, R4.1, R4.1S, R5.1, R5.1S, TP3.1
unnamed: D7.2 (A), D7.2S, J5.1, R4.2, R4.2S
unnamed: D8.2 (A), D8.2S, J2.1
unnamed: F1.1, J1.1
unnamed: Q1.3 (E), Q1.3S, Q2.1 (B)
unnamed: Q2.3 (E), Q3.2 (B), Q3.2S, R3.1
unnamed: C6.2, C6.2S, C7.2, C7.2S, Q4.2 (B), Q4.2S, R6.1, R6.1S, RV1.2, RV1.3, TP5.1
unnamed: R5.2, R5.2S, RV1.1

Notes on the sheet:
Transformer secondary 12-15 VAC, 1.5 A or more for full stereo power (12 VAC: 12 V regulated up to 0.4 A, then follows the raw rail).
Regulator: Q4 compares FB (R5 + RV1 / R6 divider of VOUT) with the 5.6 V zener and pulls the driver base down through BQ1. RV1 sets VOUT, 11.4 to 12.7 V.
J5: LED on the volume board via 2 wires (pin 1 = anode/+). Fit D7 or J5, not both.
J2: 12 V DC straight to VOUT through D8 (0.4 V drop). Bypasses the regulator and the current clamp.
Pass transistor Q2 needs a heatsink: 3.5 W at 15 VAC / 0.8 A, 3.9 W at 1.2 A (psu2.cir).
